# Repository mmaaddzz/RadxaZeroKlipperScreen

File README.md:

# RadxaZeroKlipperScreen

Compact Klipper based 3d-Printer control panel with 4 inch touch screen.

Radxa Zero: https://wiki.radxa.com/Zero

Lcd: http://www.lcdwiki.com/4.0inch_SPI_Module_ST7796

### Setup:

1. Armbian install
    1. A Install on MMC:
        Copy https://www.armbian.com/radxa-zero/ image into mmc card using eg https://gitlab.com/bztsrc/usbimager

    1. B Install on eMMC:
        1. Copy https://www.armbian.com/radxa-zero/ image and fallow https://wiki.radxa.com/Zero/install/eMMC instruction by:
            - Hold down the “USB BOOT” button on the Radxa Zero while connecting the USB cable
            - Run usb disk loader `sudo boot-g12.py rz-udisk-loader.bin`
            - Use eg https://gitlab.com/bztsrc/usbimager to load image into emulated Radxa Zero UDisk.
        2. Replace u-boot Armbian with Radxa u-boot (optional, may by done later):
            Armbian won't start from eMMC from time to time on my board with Armbian u-boot)
            - Fallow build procedure https://wiki.radxa.com/Zero/dev/u-boot or download u-boot image
                https://dl.radxa.com/zero/images/loader/u-boot.bin.sd.bin
            - Hold down the “USB BOOT” button on the Radxa Zero while connecting the USB cable
            - Run usb disk loader `sudo boot-g12.py rz-udisk-loader.bin`
            - Find /dev/sdX path to emulated Radxa Zero UDisk
                `sudo fdisk -l`
            - Copy u-boot into emulated Radxa Zero UDisk.
                `sudo dd if=u-boot.bin.sd.bin of=/dev/sdX bs=1 count=444`
                `sudo dd if=u-boot.bin.sd.bin of=/dev/sdX bs=512 skip=1 seek=1`

2. Setup Armbin
    - Connect serial terminal to Sys Uart
    - Power up and fallow Armbian setup

3. Install Lcd Driver
    1. Login and copy lcd_driver directory into board
    2. Build st7796 module
        - `cd lcd_driver/st7796`
        - `make && sudo make install`
        - verify module is working by
            `sudo modprobe st7796`
            `lsmod | grep st7796`
    3. Devicetree Overlay
        - `cd ../dtoverlay/`
        - `./install.sh`
        - reboot and verify lcd is working
    4. Install xorg
        - `sudo apt update && sudo apt install xserver-xorg-input-evdev`
        - `cd lcd_driver/xorg.conf.d/`
        - `sudo cp 99-calibration.conf /usr/share/X11/xorg.conf.d`
        - `sudo cp 99-fbturbo.conf /usr/share/X11/xorg.conf.d`
        - `sudo cp /usr/share/X11/xorg.conf.d/10-evdev.conf /usr/share/X11/xorg.conf.d/45-evdev.conf # fix for touch issue`

4. Use https://github.com/th33xitus/kiauh to install Klipper and KlipperScrean
    - check /dev/fbX device, see: https://klipperscreen.readthedocs.io/en/latest/Troubleshooting/#screen-shows-console-instead-of-klipperscreen
    - Aux Uart is /dev/ttyAML6

TODO:
    1. check spi errors: st7796 spi0.0: SPI transfer timed out
    2. improve cleanup kernel module
    3. use DKMS to moudule auto rebuild
    4. add freecad 3d models

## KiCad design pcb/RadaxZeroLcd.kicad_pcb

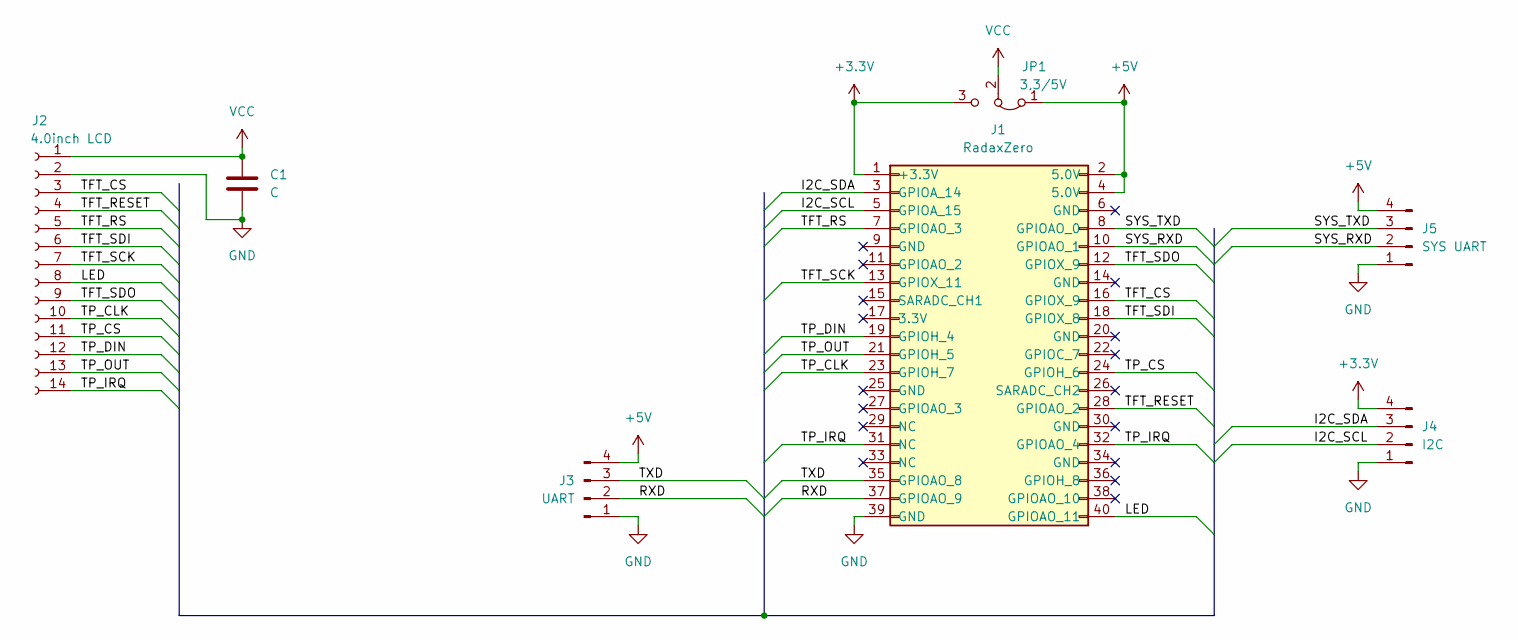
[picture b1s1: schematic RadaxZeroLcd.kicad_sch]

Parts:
C1: C; C_0805_2012Metric
J1: RadaxZero; PinSocket_2x20_P2.54mm_Vertical
J2: 4.0inch LCD; PinSocket_1x14_P2.54mm_Horizontal
J3: UART; PinHeader_1x04_P2.54mm_Horizontal
J4: I2C; PinHeader_1x04_P2.54mm_Horizontal
J5: SYS UART; PinHeader_1x04_P2.54mm_Horizontal
JP1: 3,3/5V; SolderJumper-3_P1.3mm_Open_RoundedPad1.0x1.5mm

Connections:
+3.3V: J1.1 (+3.3V), J4.4, JP1.3 (B)
+5V: J1.2 (5.0V), J1.4 (5.0V), J3.4, J5.4, JP1.1 (A)
/I2C_SCL: J1.5 (GPIOA_15), J4.2
/I2C_SDA: J1.3 (GPIOA_14), J4.3
/LED: J1.40 (GPIOAO_11), J2.8
/RXD: J1.37 (GPIOAO_9), J3.2
/SYS_RXD: J1.10 (GPIOAO_1), J5.2
/SYS_TXD: J1.8 (GPIOAO_0), J5.3
/TFT_CS: J1.16 (GPIOX_9), J2.3
/TFT_RESET: J1.28 (GPIOAO_2), J2.4
/TFT_RS: J1.7 (GPIOAO_3), J2.5
/TFT_SCK: J1.13 (GPIOX_11), J2.7
/TFT_SDI: J1.18 (GPIOX_8), J2.6
/TFT_SDO: J1.12 (GPIOX_9), J2.9
/TP_CLK: J1.23 (GPIOH_7), J2.10
/TP_CS: J1.24 (GPIOH_6), J2.11
/TP_DIN: J1.19 (GPIOH_4), J2.12
/TP_IRQ: J1.31 (NC), J1.32 (GPIOAO_4), J2.14
/TP_OUT: J1.21 (GPIOH_5), J2.13
/TXD: J1.35 (GPIOAO_8), J3.3
GND: C1.2, J1.39 (GND), J2.2, J3.1, J4.1, J5.1
VCC: C1.1, J2.1, JP1.2 (C)

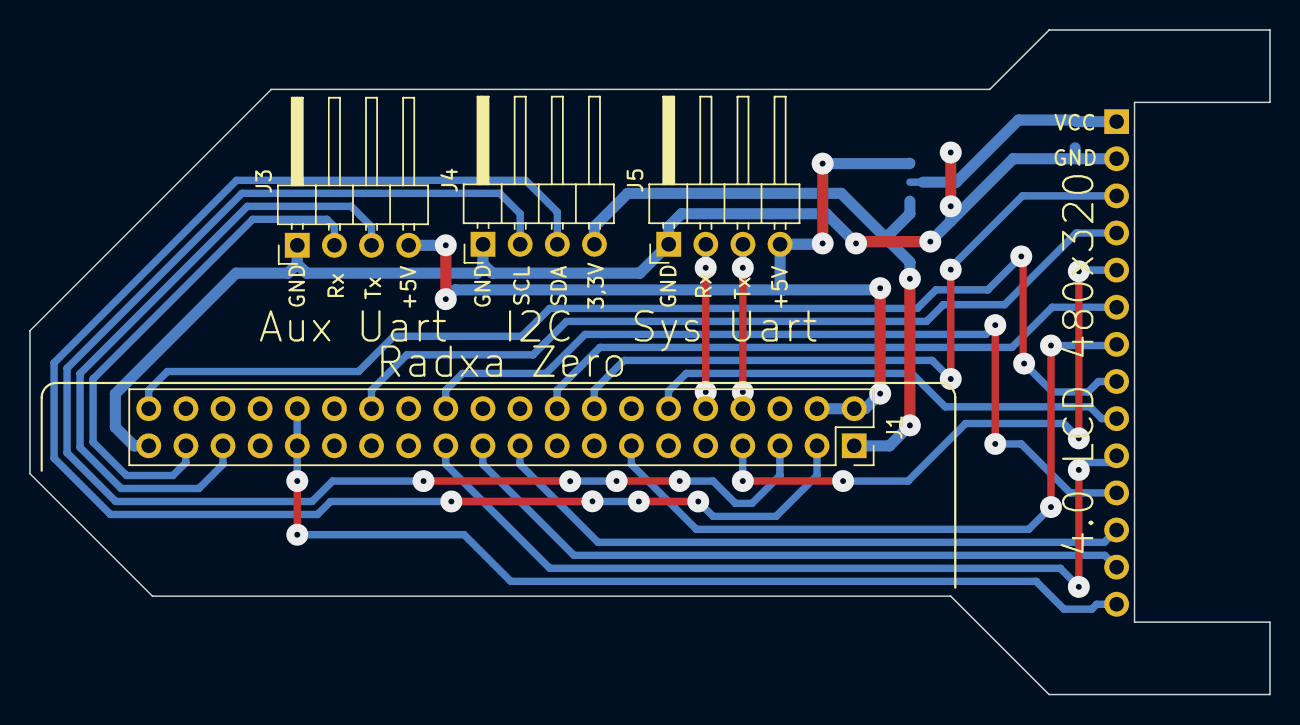
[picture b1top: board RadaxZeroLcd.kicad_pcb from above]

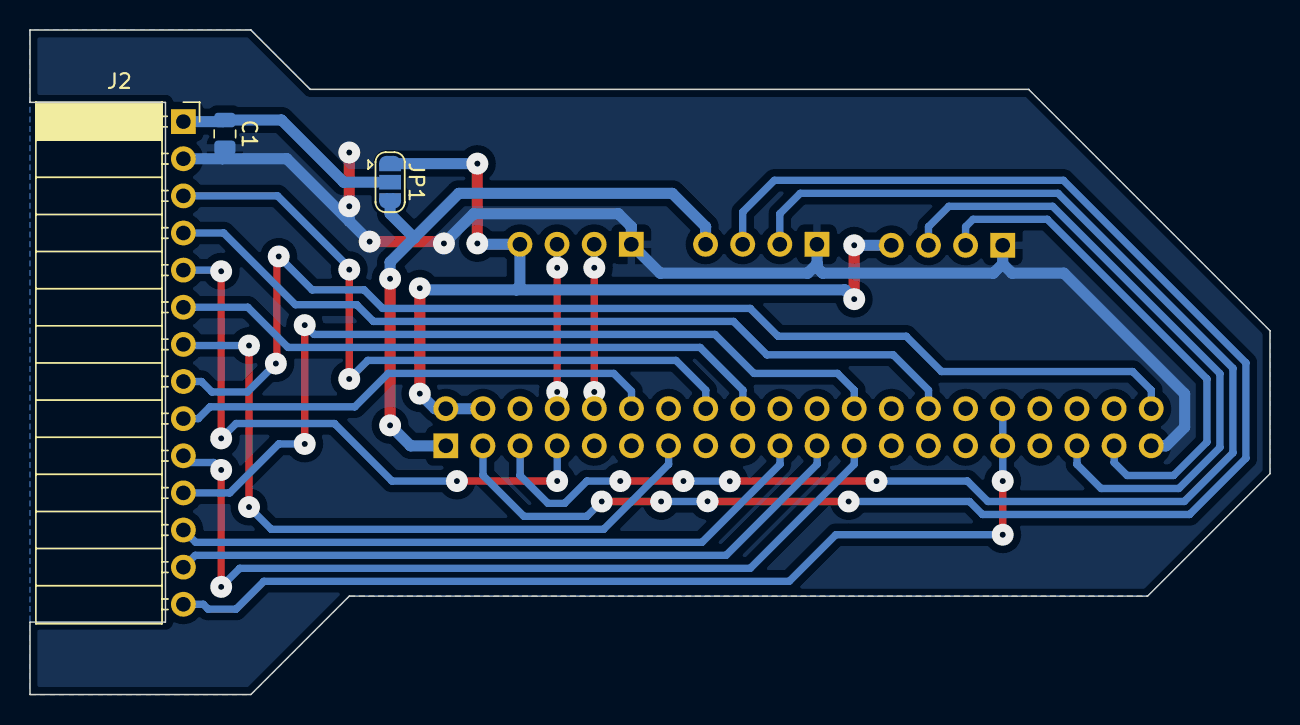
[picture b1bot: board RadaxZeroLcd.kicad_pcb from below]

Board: 2 copper layers, 84.8 x 45.5 mm, 7 parts (3 on the bottom side), 22 nets.

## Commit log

2023-01-03 pcb project upload
2023-01-03 update radxa zero footprint
2023-01-04 Module driver, Kernel DTO and setup instruction
2023-04-04 fix compilation issues on kernel v6.2.0
